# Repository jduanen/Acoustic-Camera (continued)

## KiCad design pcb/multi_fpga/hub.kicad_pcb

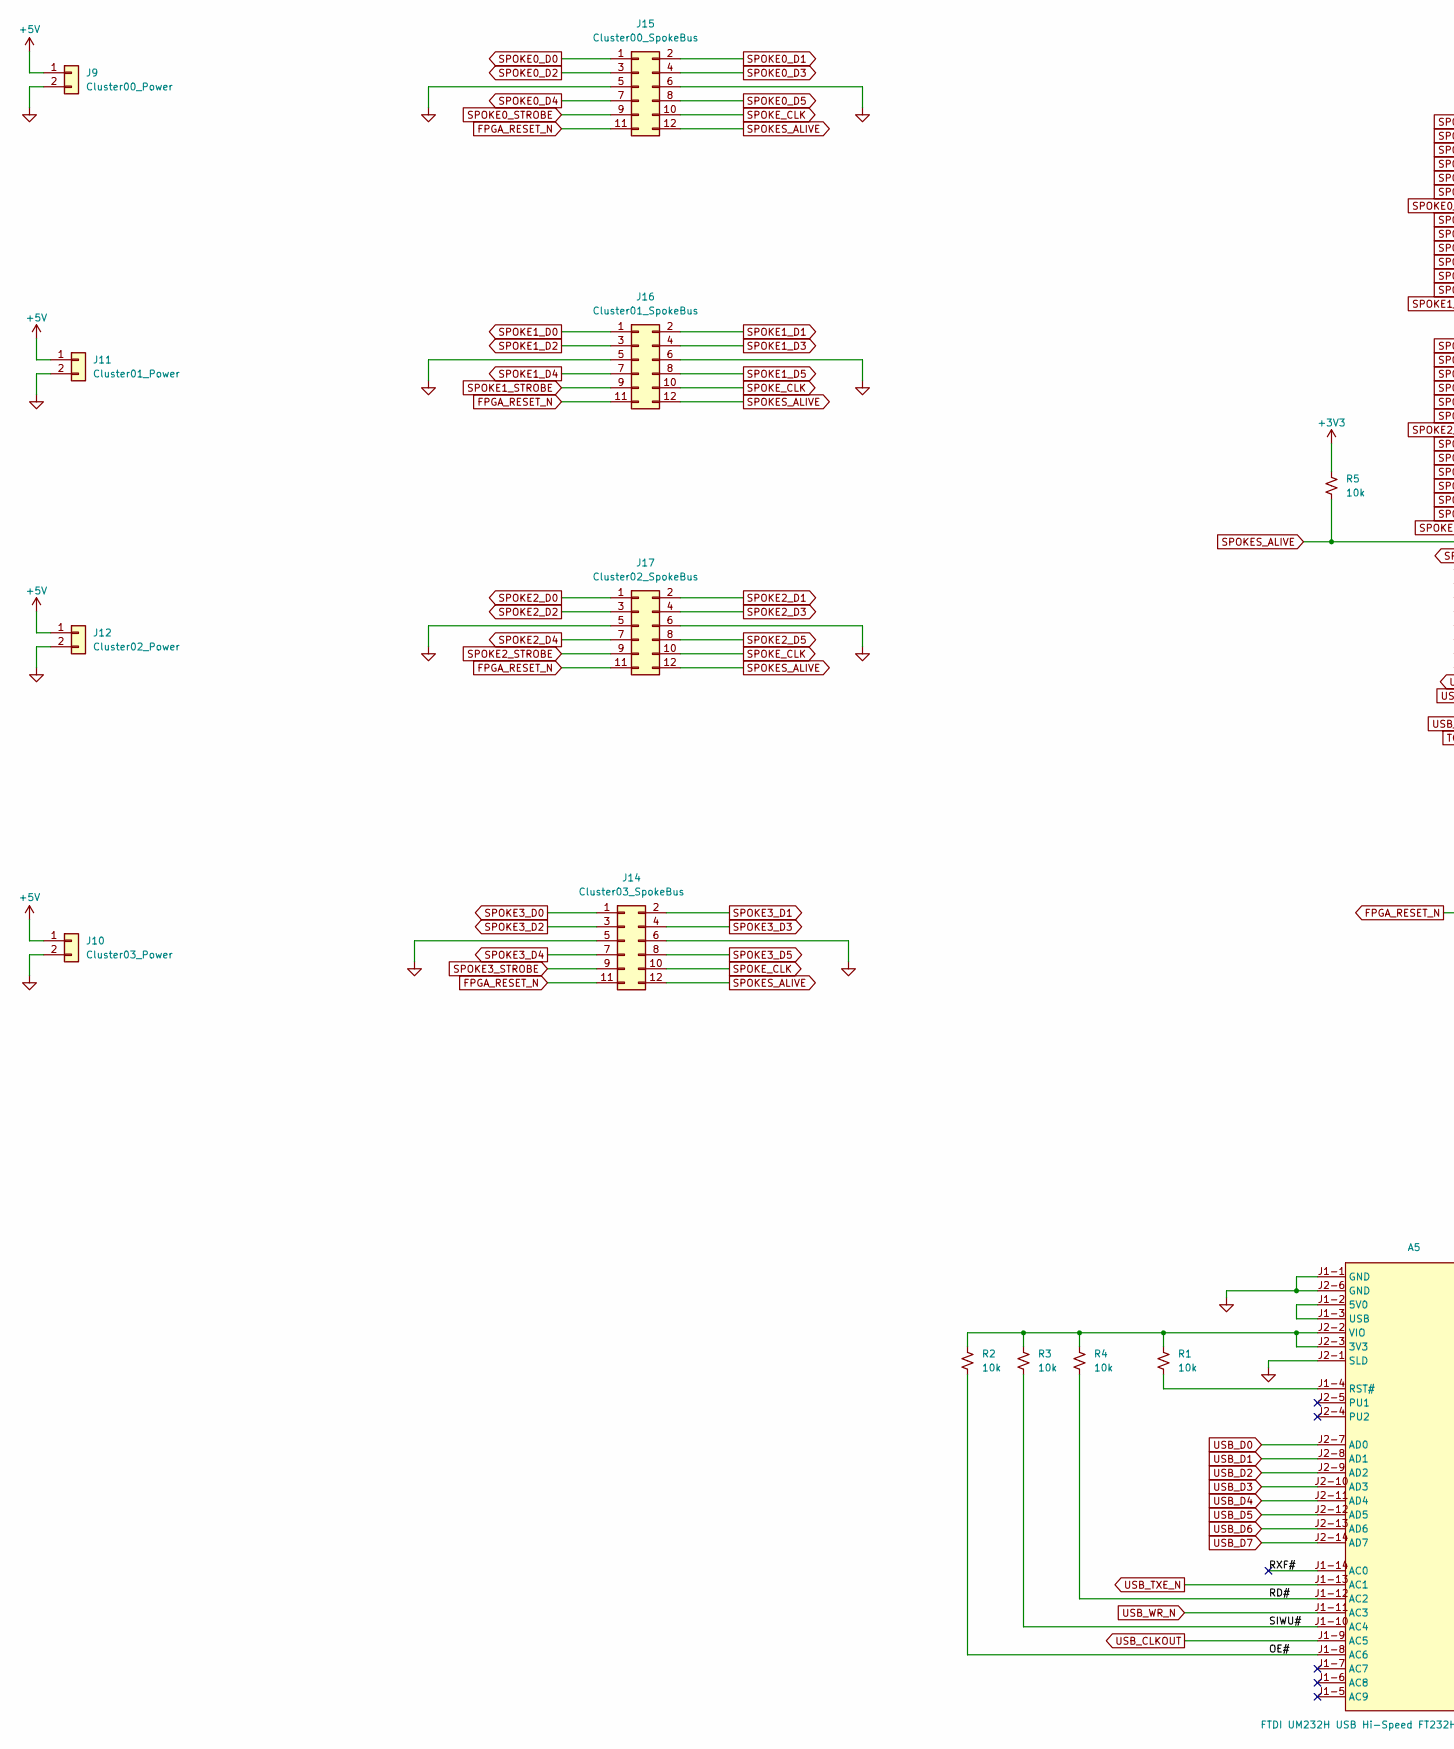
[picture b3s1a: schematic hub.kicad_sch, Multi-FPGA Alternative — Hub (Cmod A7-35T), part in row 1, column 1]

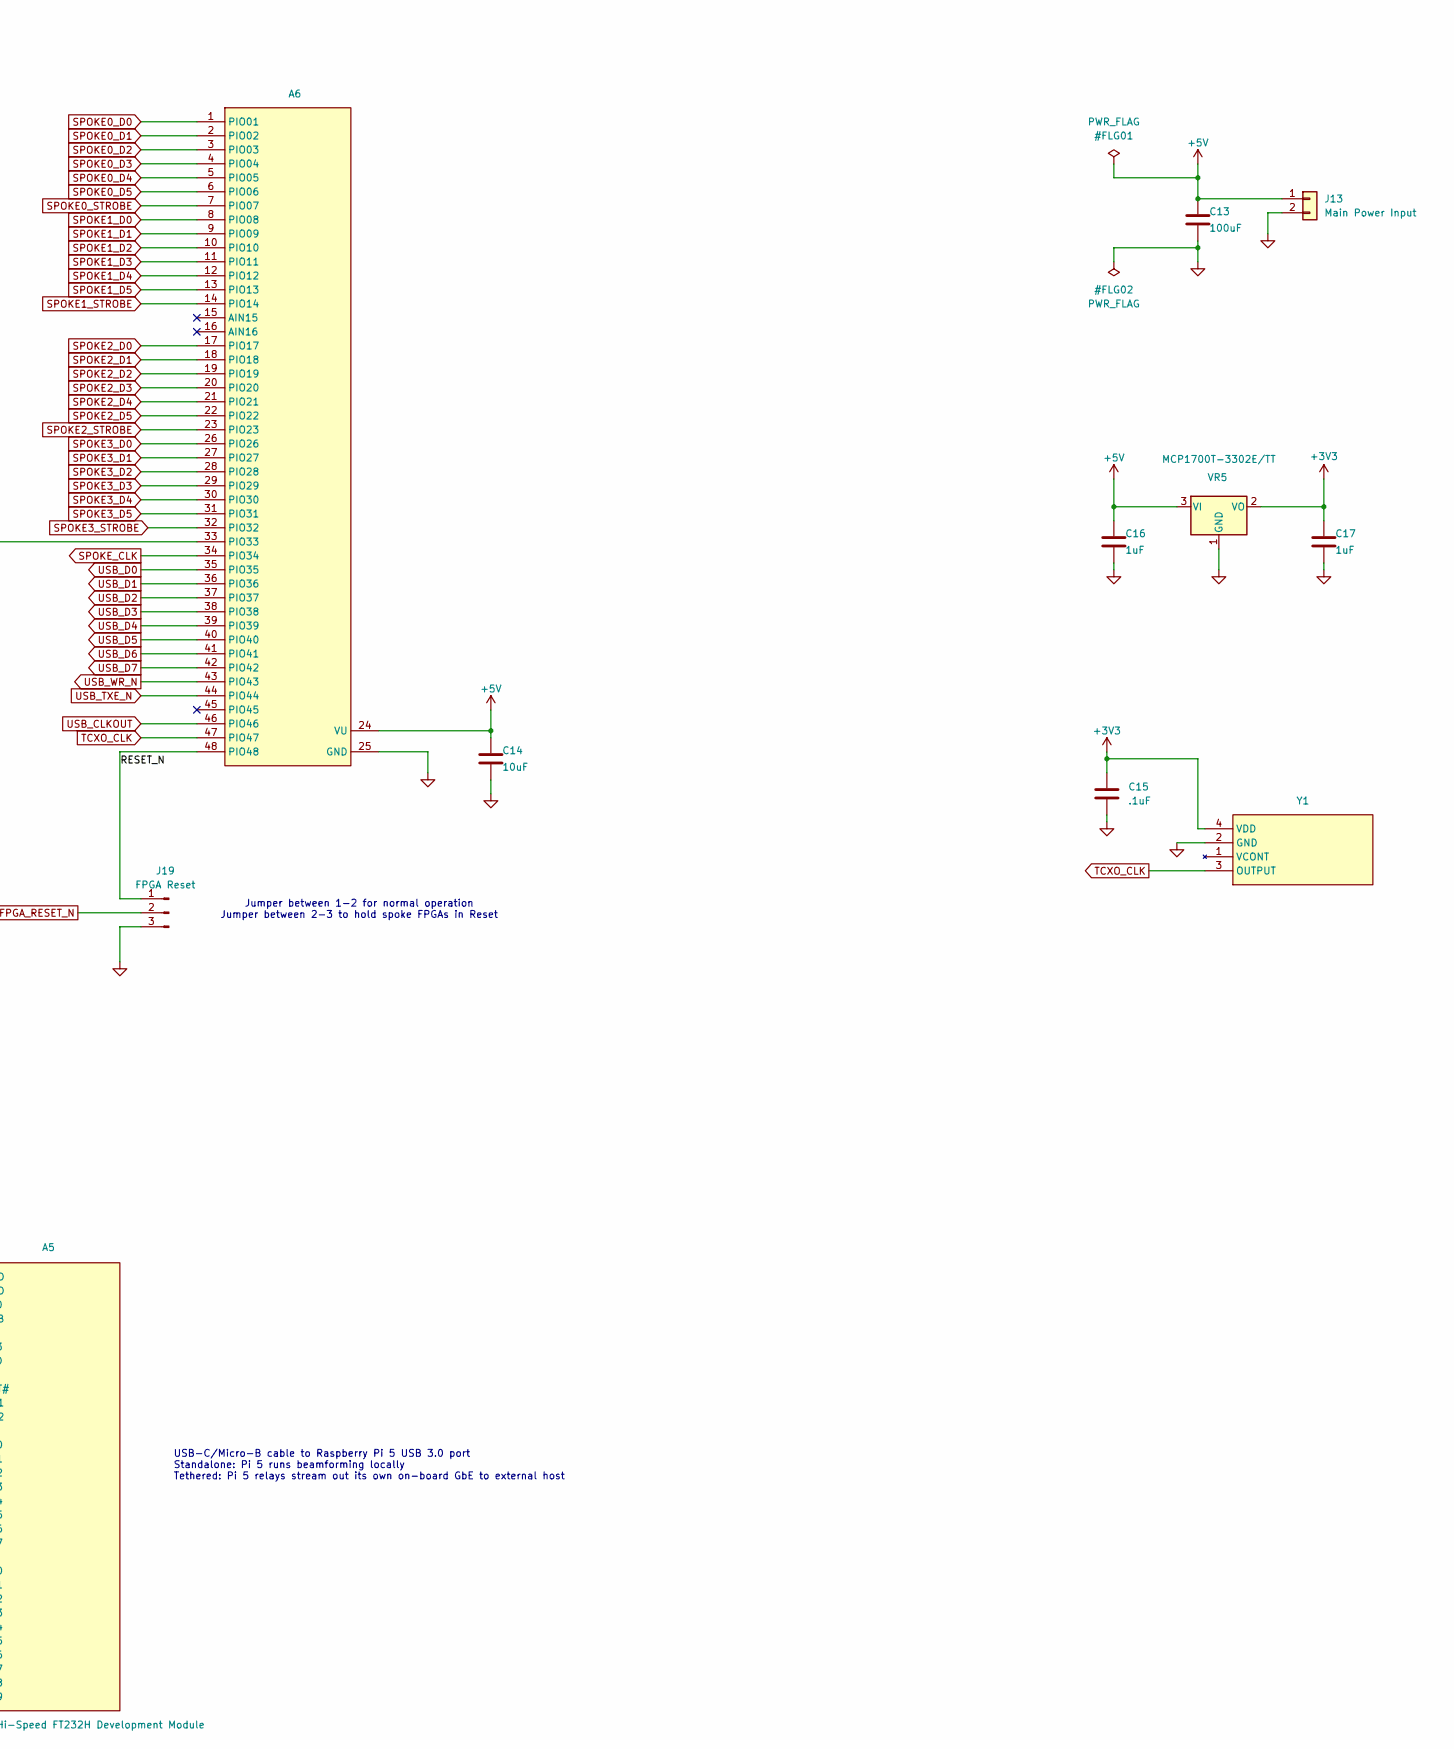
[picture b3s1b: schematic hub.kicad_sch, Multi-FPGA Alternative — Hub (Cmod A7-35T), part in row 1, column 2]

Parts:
A5: FTDI UM232H USB Hi-Speed FT232H Development Module; UM232H
A6: DIP-48_W15.24mm_Socket
C13: 100uF; CP_Elec_10x10
C14: 10uF; C_1206_3216Metric
C15: .1uF; C_0603_1608Metric
C16, C17: 1uF; C_1206_3216Metric
J9: Cluster00_Power; PinSocket_1x02_P2.54mm_Vertical
J10: Cluster03_Power; PinSocket_1x02_P2.54mm_Vertical
J11: Cluster01_Power; PinSocket_1x02_P2.54mm_Vertical
J12: Cluster02_Power; PinSocket_1x02_P2.54mm_Vertical
J13: Main Power Input; JST_XH_B2B-XH-A_1x02_P2.50mm_Vertical
J14: Cluster03_SpokeBus; PinSocket_2x06_P2.54mm_Vertical
J15: Cluster00_SpokeBus; PinSocket_2x06_P2.54mm_Vertical
J16: Cluster01_SpokeBus; PinSocket_2x06_P2.54mm_Vertical
J17: Cluster02_SpokeBus; PinSocket_2x06_P2.54mm_Vertical
J19: FPGA Reset; PinHeader_1x03_P2.54mm_Vertical
R1, R2, R3, R4, R5: 10k; R_0603_1608Metric
VR5: MCP1700T-3302E/TT; SOT-23
Y1: ECS-TXO-5032-122.8-TR

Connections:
+3V3: C15.1, C17.1, R5.2, VR5.2 (VO), Y1.4 (VDD)
+5V: A6.24 (VU), C13.1, C14.1, C16.1, J9.1, J10.1, J11.1, J12.1, J13.1, VR5.3 (VI)
/OE#: A5.J1-8 (AC6), R2.1
/RD#: A5.J1-12 (AC2), R4.1
/RESET_N: A6.48 (PIO48), J19.1
/RXF#: A5.J1-14 (AC0)
/SIWU#: A5.J1-10 (AC4), R3.1
FPGA_RESET_N: J14.11, J15.11, J16.11, J17.11, J19.2
GND: A5.J1-1 (GND), A5.J2-1 (SLD), A5.J2-6 (GND), A6.25 (GND), C13.2, C14.2, C15.2, C16.2, C17.2, J9.2, J10.2, J11.2, J12.2, J13.2, J14.5, J14.6, J15.5, J15.6, J16.5, J16.6, J17.5, J17.6, J19.3, VR5.1 (GND), Y1.2 (GND)
unnamed: A5.J2-2 (VIO), A5.J2-3 (3V3), R1.2, R2.2, R3.2, R4.2
unnamed: A5.J1-2 (5V0), A5.J1-3 (USB)
unnamed: A5.J1-4 (RST#), R1.1
SPOKE0_D0: A6.1 (PIO01), J15.1
SPOKE0_D1: A6.2 (PIO02), J15.2
SPOKE0_D2: A6.3 (PIO03), J15.3
SPOKE0_D3: A6.4 (PIO04), J15.4
SPOKE0_D4: A6.5 (PIO05), J15.7
SPOKE0_D5: A6.6 (PIO06), J15.8
SPOKE0_STROBE: A6.7 (PIO07), J15.9
SPOKE1_D0: A6.8 (PIO08), J16.1
SPOKE1_D1: A6.9 (PIO09), J16.2
SPOKE1_D2: A6.10 (PIO10), J16.3
SPOKE1_D3: A6.11 (PIO11), J16.4
SPOKE1_D4: A6.12 (PIO12), J16.7
SPOKE1_D5: A6.13 (PIO13), J16.8
SPOKE1_STROBE: A6.14 (PIO14), J16.9
SPOKE2_D0: A6.17 (PIO17), J17.1
SPOKE2_D1: A6.18 (PIO18), J17.2
SPOKE2_D2: A6.19 (PIO19), J17.3
SPOKE2_D3: A6.20 (PIO20), J17.4
SPOKE2_D4: A6.21 (PIO21), J17.7
SPOKE2_D5: A6.22 (PIO22), J17.8
SPOKE2_STROBE: A6.23 (PIO23), J17.9
SPOKE3_D0: A6.26 (PIO26), J14.1
SPOKE3_D1: A6.27 (PIO27), J14.2
SPOKE3_D2: A6.28 (PIO28), J14.3
SPOKE3_D3: A6.29 (PIO29), J14.4
SPOKE3_D4: A6.30 (PIO30), J14.7
SPOKE3_D5: A6.31 (PIO31), J14.8
SPOKE3_STROBE: A6.32 (PIO32), J14.9
SPOKES_ALIVE: A6.33 (PIO33), J14.12, J15.12, J16.12, J17.12, R5.1
SPOKE_CLK: A6.34 (PIO34), J14.10, J15.10, J16.10, J17.10
TCXO_CLK: A6.47 (PIO47), Y1.3 (OUTPUT)
USB_CLKOUT: A5.J1-9 (AC5), A6.46 (PIO46)
USB_D0: A5.J2-7 (AD0), A6.35 (PIO35)
USB_D1: A5.J2-8 (AD1), A6.36 (PIO36)
USB_D2: A5.J2-9 (AD2), A6.37 (PIO37)
USB_D3: A5.J2-10 (AD3), A6.38 (PIO38)
USB_D4: A5.J2-11 (AD4), A6.39 (PIO39)
USB_D5: A5.J2-12 (AD5), A6.40 (PIO40)
USB_D6: A5.J2-13 (AD6), A6.41 (PIO41)
USB_D7: A5.J2-14 (AD7), A6.42 (PIO42)
USB_TXE_N: A5.J1-13 (AC1), A6.44 (PIO44)
USB_WR_N: A5.J1-11 (AC3), A6.43 (PIO43)

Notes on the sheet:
USB-C/Micro-B cable to Raspberry Pi 5 USB 3.0 port Standalone: Pi 5 runs beamforming locally Tethered: Pi 5 relays stream out its own on-board GbE to external host
Jumper between 1-2 for normal operation Jumper between 2-3 to hold spoke FPGAs in Reset

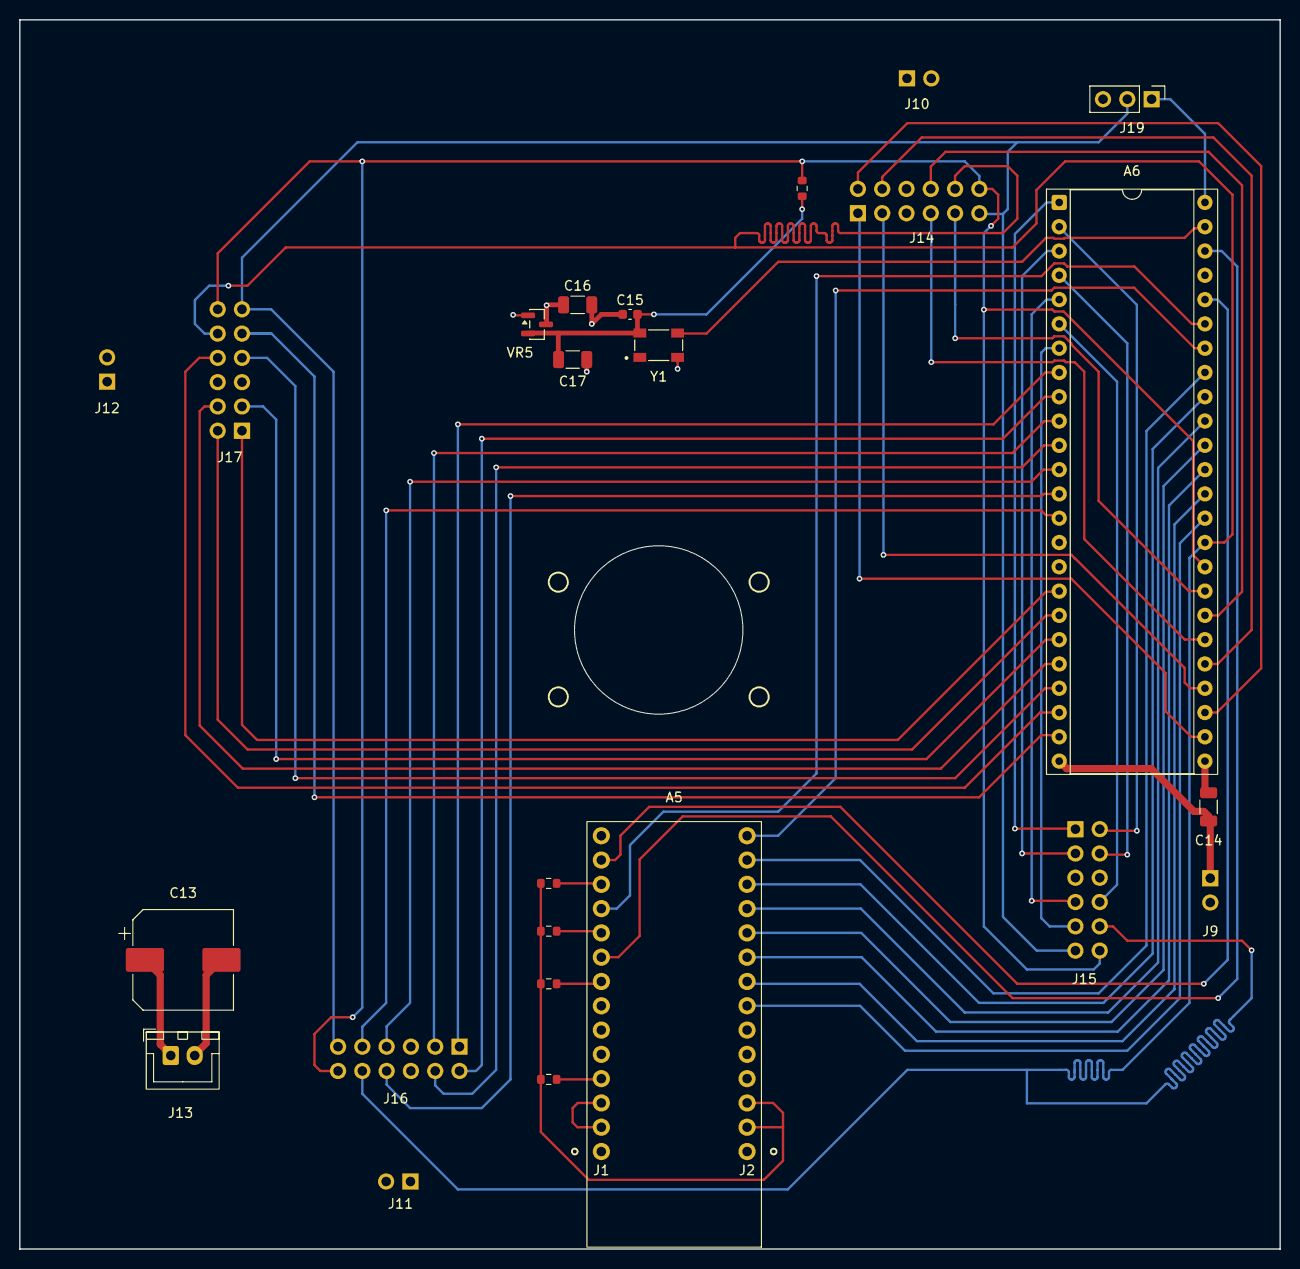
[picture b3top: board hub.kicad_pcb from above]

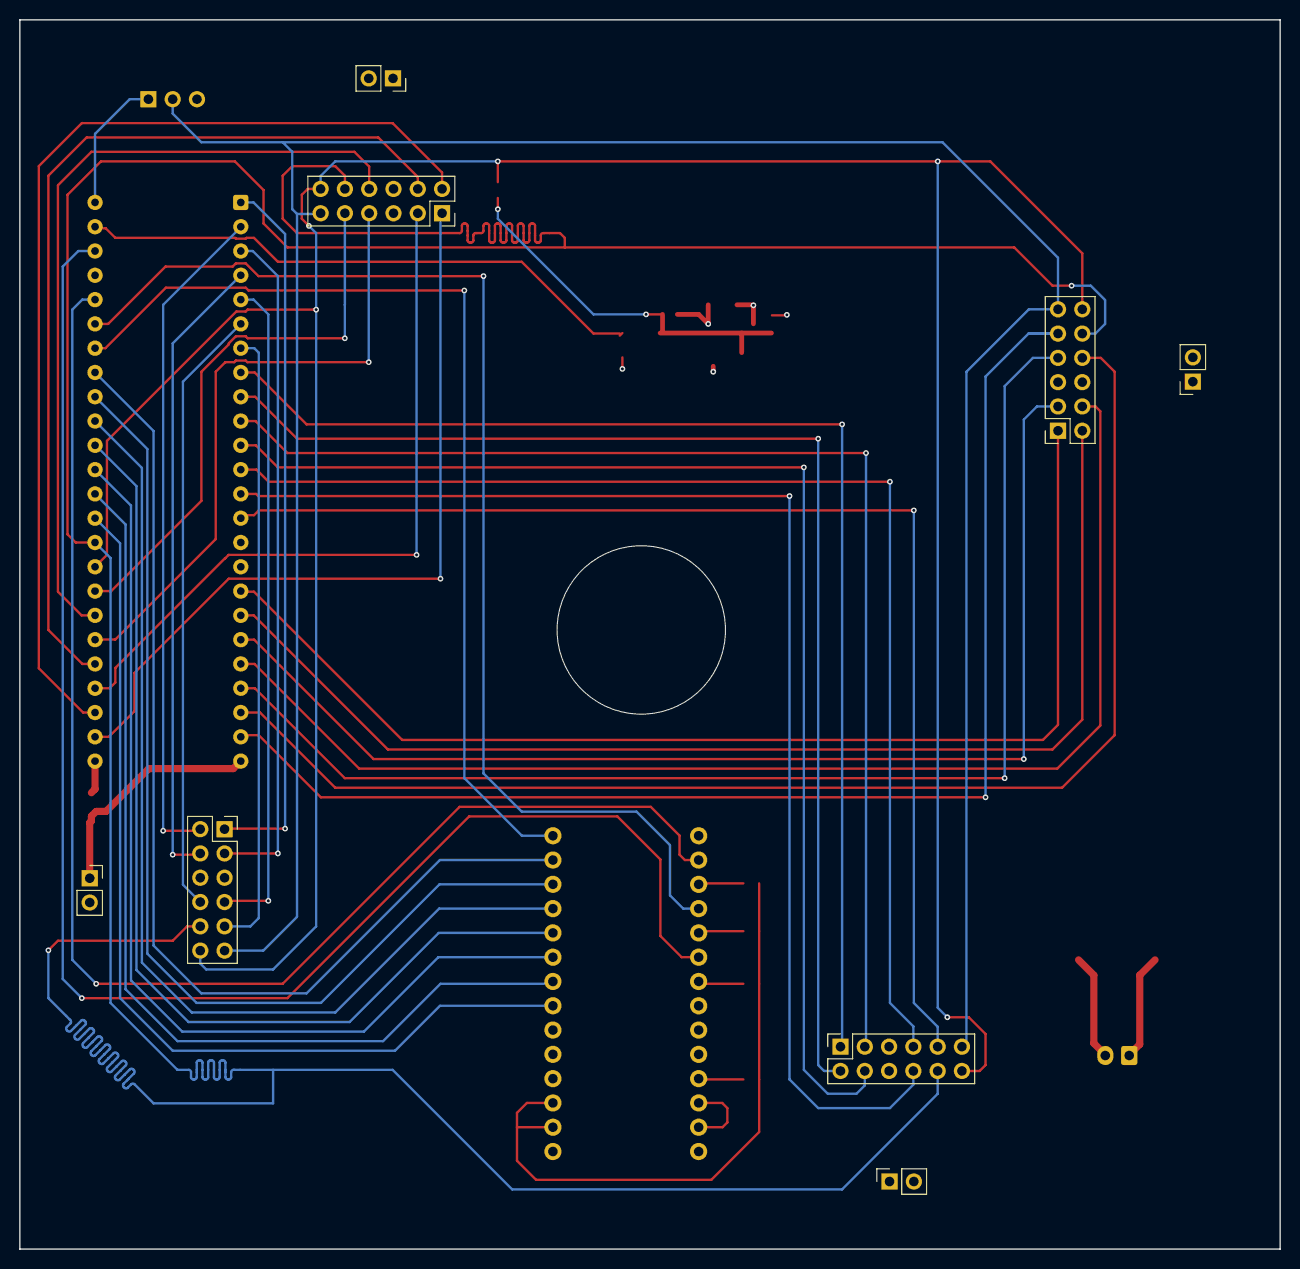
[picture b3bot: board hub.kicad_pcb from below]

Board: 4 copper layers, 131.8 x 128.5 mm, 24 parts (8 on the bottom side), 53 nets.

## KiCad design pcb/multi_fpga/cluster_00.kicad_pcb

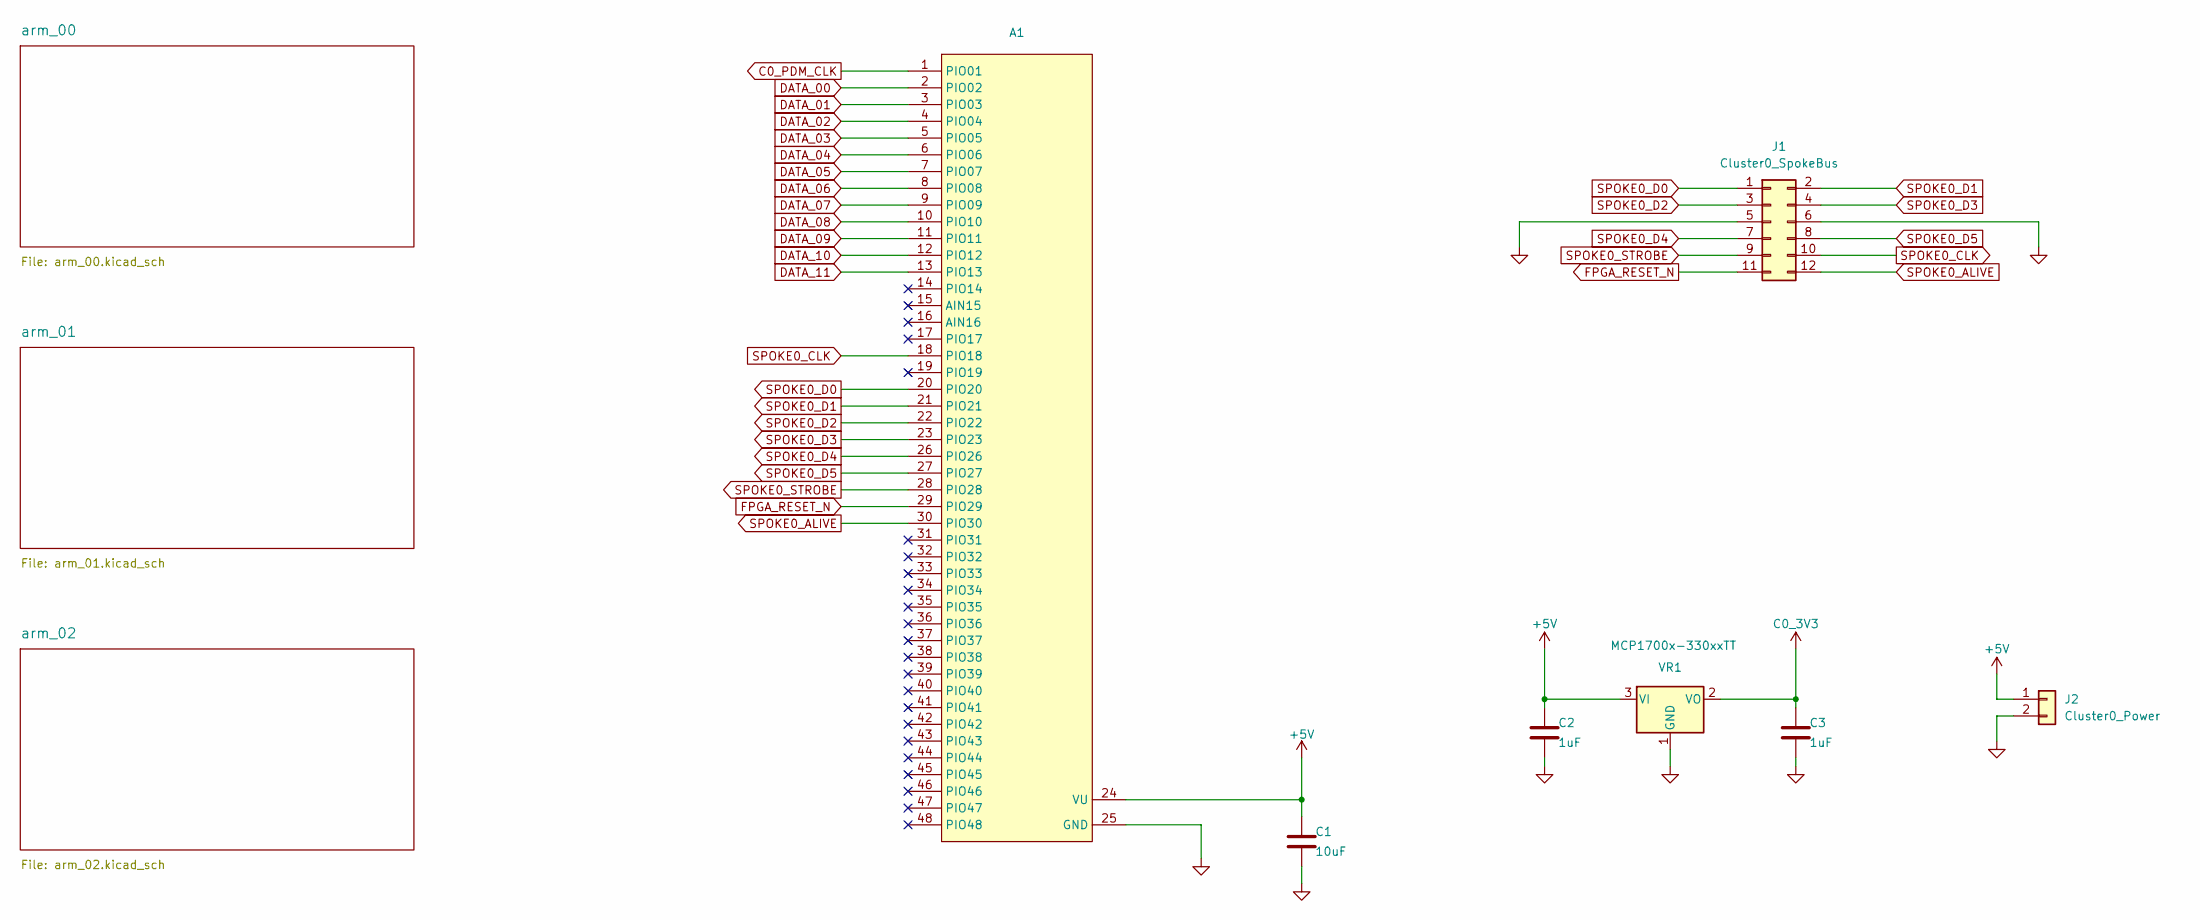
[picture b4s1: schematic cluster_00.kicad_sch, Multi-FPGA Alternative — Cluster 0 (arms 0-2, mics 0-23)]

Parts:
A1: DIP-48_W15.24mm_Socket
C1: 10uF; C_1206_3216Metric; Voltage 10V; Tolerance 20%
C2, C3: 1uF; C_0603_1608Metric
J1: Cluster0_SpokeBus; PinHeader_2x06_P2.54mm_Vertical
J2: Cluster0_Power
VR1: MCP1700x-330xxTT; SOT-23

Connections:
+5V: A1.24 (VU), C1.1, C2.1, J2.1, VR1.3 (VI)
C0_3V3: C3.1, VR1.2 (VO); also elsewhere on the board
C0_PDM_CLK: A1.1 (PIO01); also elsewhere on the board
DATA_00: A1.2 (PIO02); also elsewhere on the board
DATA_01: A1.3 (PIO03); also elsewhere on the board
DATA_02: A1.4 (PIO04); also elsewhere on the board
DATA_03: A1.5 (PIO05); also elsewhere on the board
DATA_04: A1.6 (PIO06); also elsewhere on the board
DATA_05: A1.7 (PIO07); also elsewhere on the board
DATA_06: A1.8 (PIO08); also elsewhere on the board
DATA_07: A1.9 (PIO09); also elsewhere on the board
DATA_08: A1.10 (PIO10); also elsewhere on the board
DATA_09: A1.11 (PIO11); also elsewhere on the board
DATA_10: A1.12 (PIO12); also elsewhere on the board
DATA_11: A1.13 (PIO13); also elsewhere on the board
FPGA_RESET_N: A1.29 (PIO29), J1.11
GND: A1.25 (GND), C1.2, C2.2, C3.2, J1.5, J1.6, J2.2, VR1.1 (GND); also elsewhere on the board
SPOKE0_ALIVE: A1.30 (PIO30), J1.12
SPOKE0_CLK: A1.18 (PIO18), J1.10
SPOKE0_D0: A1.20 (PIO20), J1.1
SPOKE0_D1: A1.21 (PIO21), J1.2
SPOKE0_D2: A1.22 (PIO22), J1.3
SPOKE0_D3: A1.23 (PIO23), J1.4
SPOKE0_D4: A1.26 (PIO26), J1.7
SPOKE0_D5: A1.27 (PIO27), J1.8
SPOKE0_STROBE: A1.28 (PIO28), J1.9

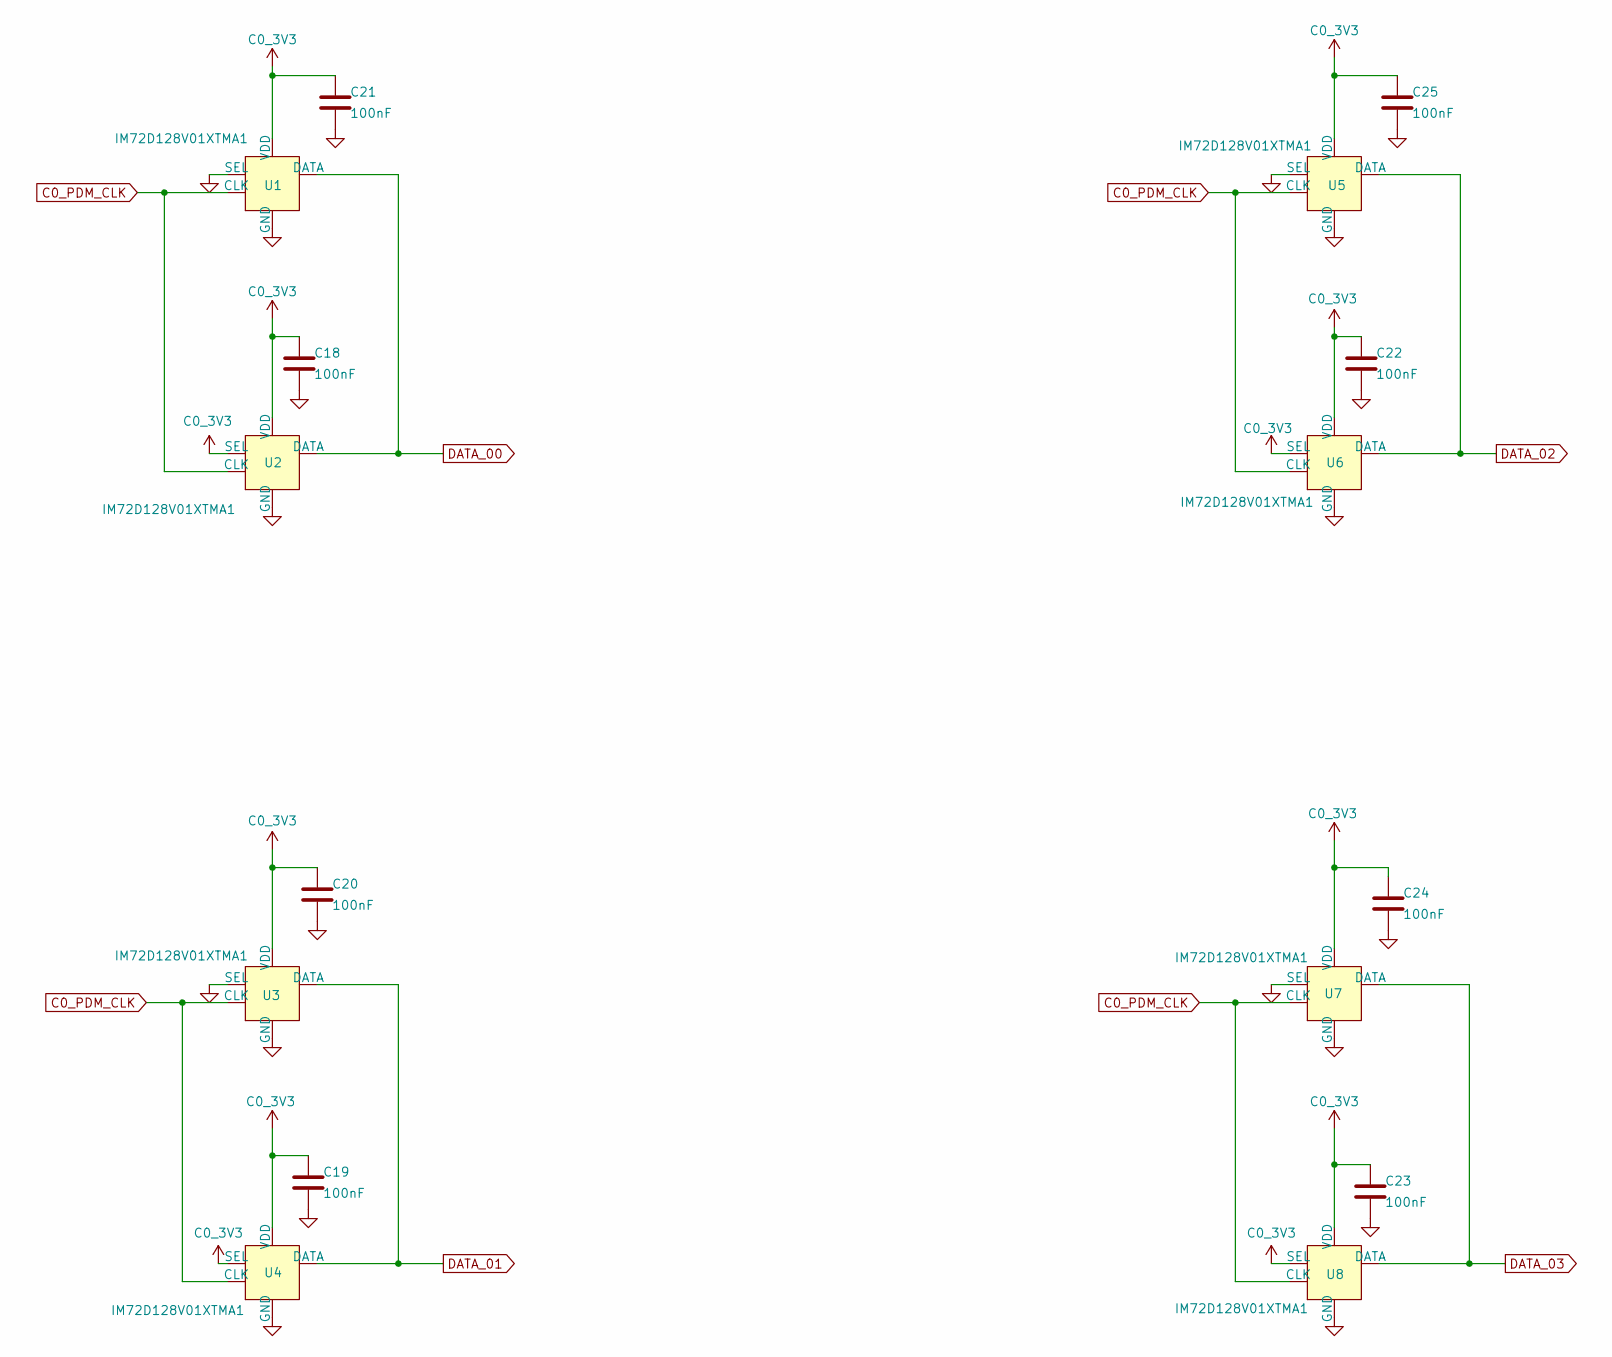
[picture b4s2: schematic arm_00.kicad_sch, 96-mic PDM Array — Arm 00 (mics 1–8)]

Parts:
C18, C19, C20, C21, C22, C23, C24, C25: 100nF; C_0603_1608Metric
U1, U2, U3, U4, U5, U6, U7, U8: IM72D128V01XTMA1

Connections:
C0_3V3: C18.1, C19.1, C20.1, C21.1, C22.1, C23.1, C24.1, C25.1, U1.2 (VDD), U2.2 (VDD), U2.4 (SEL), U3.2 (VDD), U4.2 (VDD), U4.4 (SEL), U5.2 (VDD), U6.2 (VDD), U6.4 (SEL), U7.2 (VDD), U8.2 (VDD), U8.4 (SEL); also elsewhere on the board
C0_PDM_CLK: U1.3 (CLK), U2.3 (CLK), U3.3 (CLK), U4.3 (CLK), U5.3 (CLK), U6.3 (CLK), U7.3 (CLK), U8.3 (CLK); also elsewhere on the board
DATA_00: U1.1 (DATA), U2.1 (DATA); also elsewhere on the board
DATA_01: U3.1 (DATA), U4.1 (DATA); also elsewhere on the board
DATA_02: U5.1 (DATA), U6.1 (DATA); also elsewhere on the board
DATA_03: U7.1 (DATA), U8.1 (DATA); also elsewhere on the board
GND: C18.2, C19.2, C20.2, C21.2, C22.2, C23.2, C24.2, C25.2, U1.4 (SEL), U1.5 (GND), U2.5 (GND), U3.4 (SEL), U3.5 (GND), U4.5 (GND), U5.4 (SEL), U5.5 (GND), U6.5 (GND), U7.4 (SEL), U7.5 (GND), U8.5 (GND); also elsewhere on the board

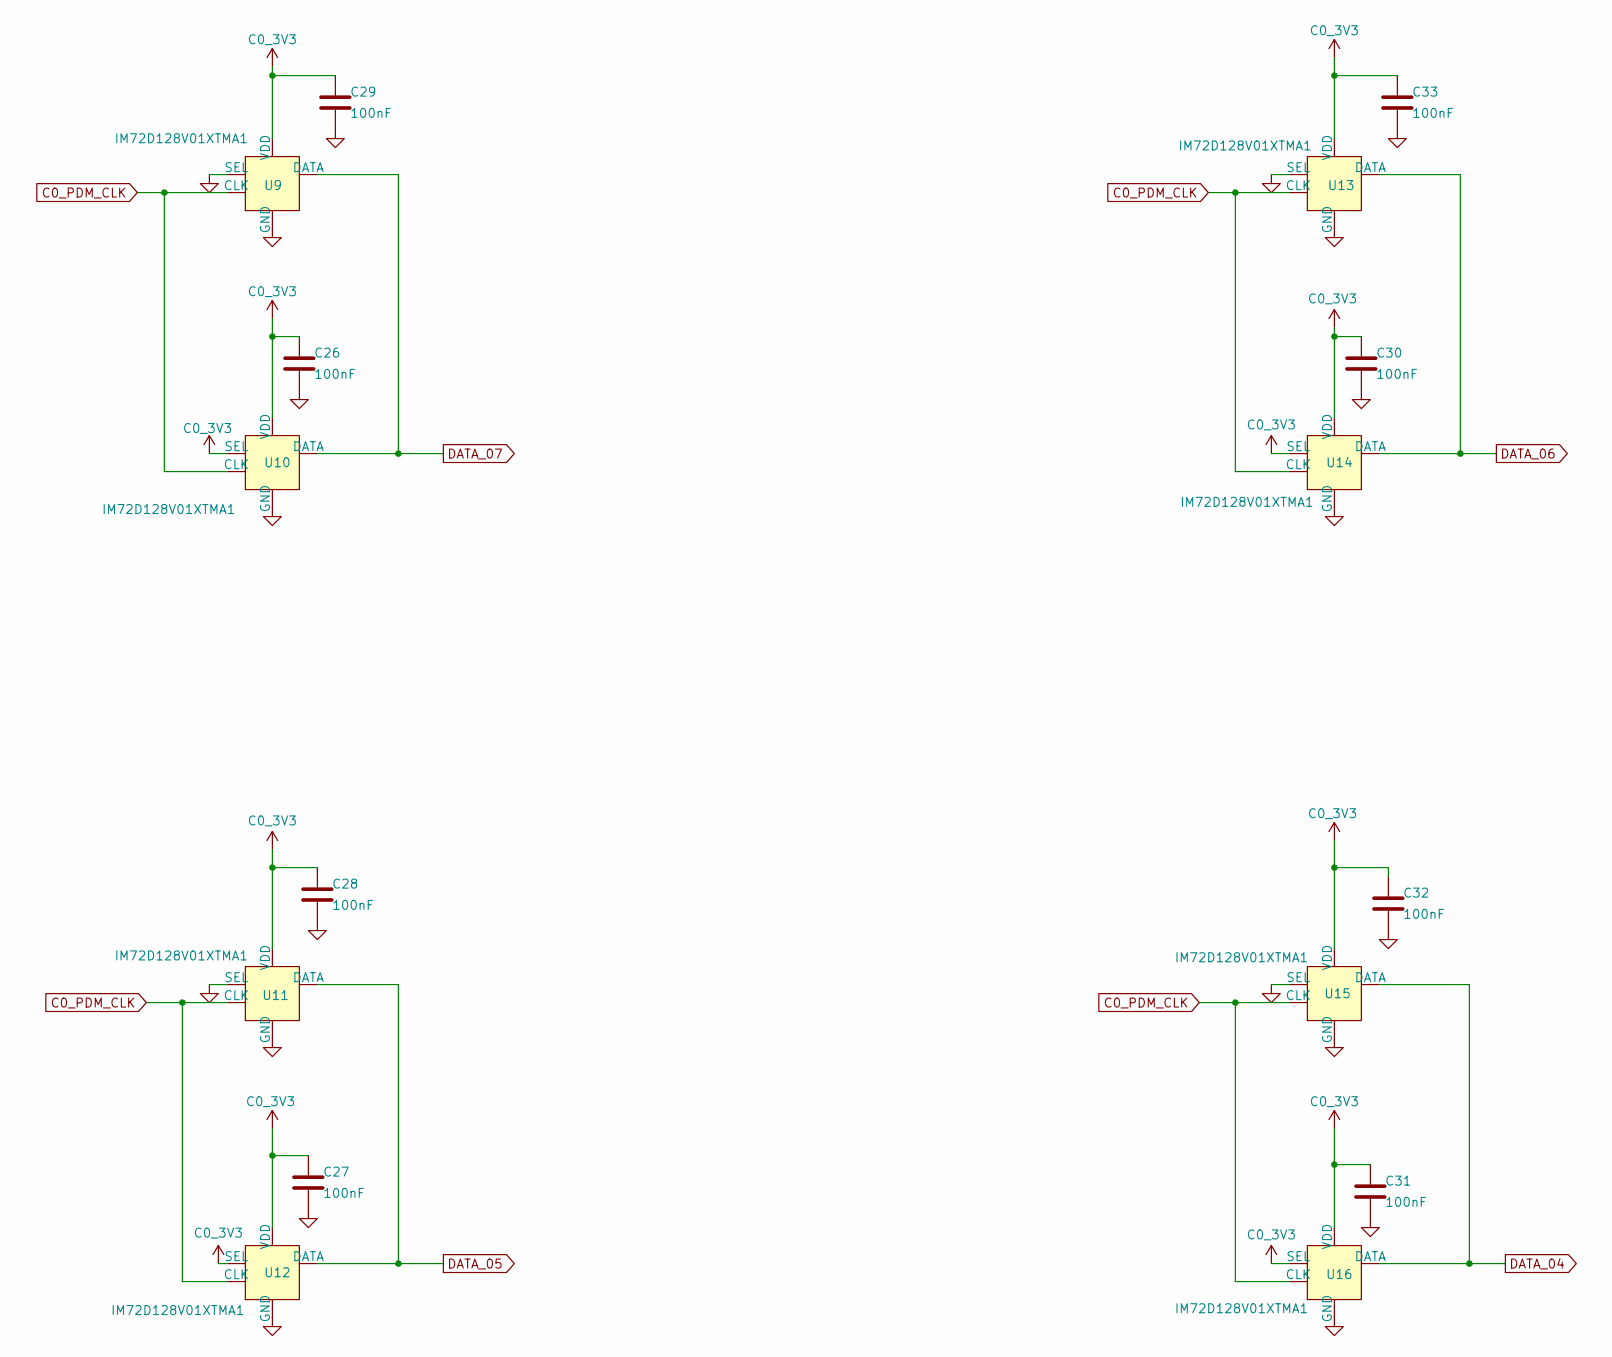
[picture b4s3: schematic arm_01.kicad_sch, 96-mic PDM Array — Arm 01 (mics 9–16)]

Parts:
C26, C27, C28, C29, C30, C31, C32, C33: 100nF; C_0603_1608Metric
U9, U10, U11, U12, U13, U14, U15, U16: IM72D128V01XTMA1

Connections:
C0_3V3: C26.1, C27.1, C28.1, C29.1, C30.1, C31.1, C32.1, C33.1, U9.2 (VDD), U10.2 (VDD), U10.4 (SEL), U11.2 (VDD), U12.2 (VDD), U12.4 (SEL), U13.2 (VDD), U14.2 (VDD), U14.4 (SEL), U15.2 (VDD), U16.2 (VDD), U16.4 (SEL); also elsewhere on the board
C0_PDM_CLK: U9.3 (CLK), U10.3 (CLK), U11.3 (CLK), U12.3 (CLK), U13.3 (CLK), U14.3 (CLK), U15.3 (CLK), U16.3 (CLK); also elsewhere on the board
DATA_04: U15.1 (DATA), U16.1 (DATA); also elsewhere on the board
DATA_05: U11.1 (DATA), U12.1 (DATA); also elsewhere on the board
DATA_06: U13.1 (DATA), U14.1 (DATA); also elsewhere on the board
DATA_07: U9.1 (DATA), U10.1 (DATA); also elsewhere on the board
GND: C26.2, C27.2, C28.2, C29.2, C30.2, C31.2, C32.2, C33.2, U9.4 (SEL), U9.5 (GND), U10.5 (GND), U11.4 (SEL), U11.5 (GND), U12.5 (GND), U13.4 (SEL), U13.5 (GND), U14.5 (GND), U15.4 (SEL), U15.5 (GND), U16.5 (GND); also elsewhere on the board

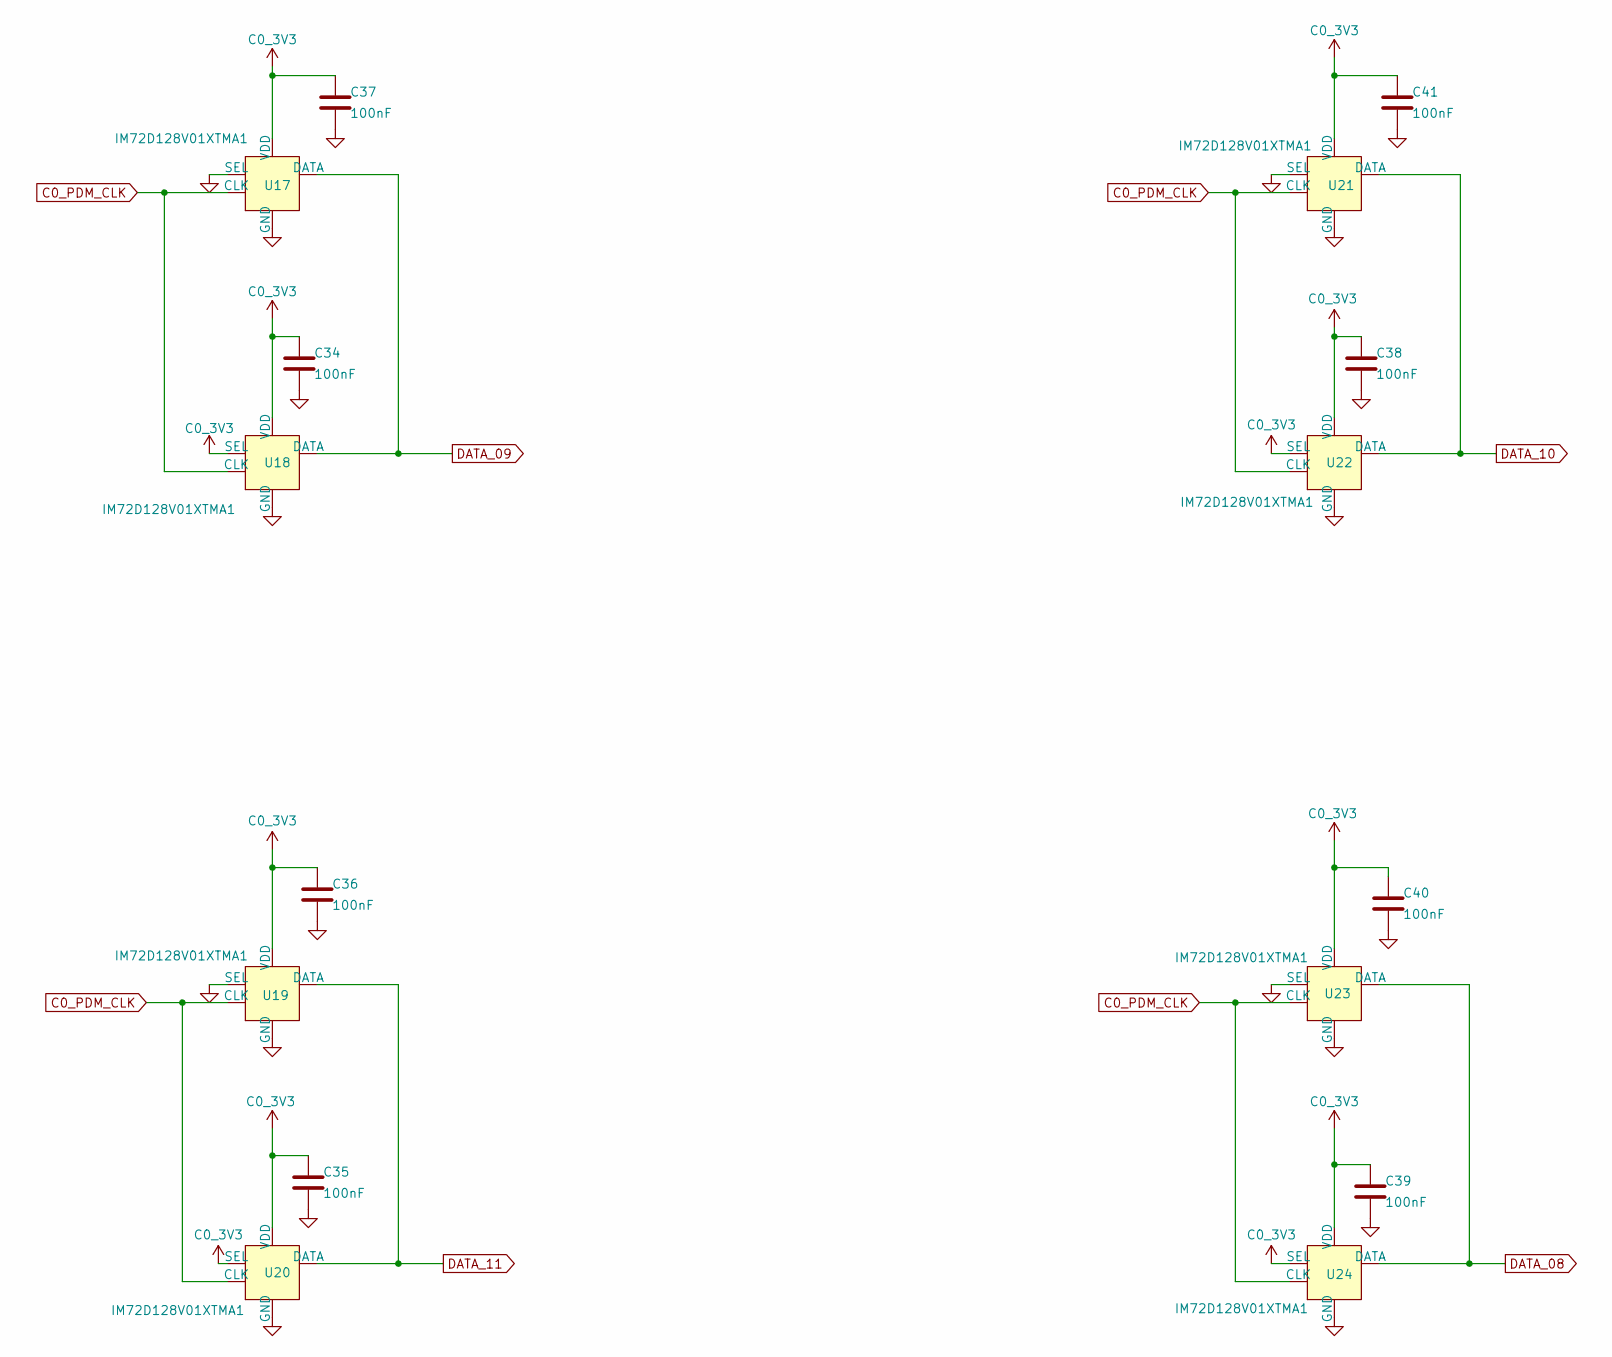
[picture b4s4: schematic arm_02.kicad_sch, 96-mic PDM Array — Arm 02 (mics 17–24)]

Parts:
C34, C35, C36, C37, C38, C39, C40, C41: 100nF; C_0603_1608Metric
U17, U18, U19, U20, U21, U22, U23, U24: IM72D128V01XTMA1

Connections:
C0_3V3: C34.1, C35.1, C36.1, C37.1, C38.1, C39.1, C40.1, C41.1, U17.2 (VDD), U18.2 (VDD), U18.4 (SEL), U19.2 (VDD), U20.2 (VDD), U20.4 (SEL), U21.2 (VDD), U22.2 (VDD), U22.4 (SEL), U23.2 (VDD), U24.2 (VDD), U24.4 (SEL); also elsewhere on the board
C0_PDM_CLK: U17.3 (CLK), U18.3 (CLK), U19.3 (CLK), U20.3 (CLK), U21.3 (CLK), U22.3 (CLK), U23.3 (CLK), U24.3 (CLK); also elsewhere on the board
DATA_08: U23.1 (DATA), U24.1 (DATA); also elsewhere on the board
DATA_09: U17.1 (DATA), U18.1 (DATA); also elsewhere on the board
DATA_10: U21.1 (DATA), U22.1 (DATA); also elsewhere on the board
DATA_11: U19.1 (DATA), U20.1 (DATA); also elsewhere on the board
GND: C34.2, C35.2, C36.2, C37.2, C38.2, C39.2, C40.2, C41.2, U17.4 (SEL), U17.5 (GND), U18.5 (GND), U19.4 (SEL), U19.5 (GND), U20.5 (GND), U21.4 (SEL), U21.5 (GND), U22.5 (GND), U23.4 (SEL), U23.5 (GND), U24.5 (GND); also elsewhere on the board
